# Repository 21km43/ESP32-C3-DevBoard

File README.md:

# ESP32-C3-DevBoard
ESP32-C3 Development Board. Made with [KiCAD 9.0](https://KiCAD.org)

You can get ESP32-C3-WROOM-02 from here.  
* [秋月電子](https://akizukidenshi.com/catalog/g/gM-17493/)  
* [DigiKey](https://www.digikey.jp/ja/products/detail/espressif-systems/ESP32-C3-WROOM-02-N4/14553031)
* [Mouser](https://www.mouser.jp/ProductDetail/Espressif-Systems/ESP32-C3-WROOM-02-N4?qs=stqOd1AaK7%2FqjTZKEOgfUg%3D%3D)

Orders can be placed by uploading data(Gerber, BOM, and CPL) to the JLCPCB. 
This project uses [Espressif Library for KiCAD](https://github.com/espressif/kicad-libraries). (It is available on Plugin & Contents manager.)  
Gerber, bom and cpl is placed on [production folder](/production) directory and Release. 

## Features
* Upload method: USB (Do not use GPIO 18 and 19 when downloading)
* USB: Type-C (USB 2.0)
* Regulator: [RT9080-33GJ5](https://www.richtek.com/Products/Linear%20Regulator/Single%20Output%20Linear%20Regulator/RT9080?sc_lang=en).
* External input voltage range: 4.3-6.5V (4.5V-5.5V is recommended)
* Power consumption (in deep sleep): 11.5µA (ESP32-C3: 5µA, RT9080-33GJ5: 6.5µA)

### Solder Jumpers
* JP1 ... VBUS = 5V jumper (Default: not connected): Connecting this disables the protective SBD between USB and external power supply. To eliminate the voltage drop due to SBD and output the voltage input from USB as it is to 5V, connect this jumper. Note that shorting this pin will increase current consumption by about 0.1mA due to the pull-down resistor on the CC pin.
* JP2 ... 5V -> 3.3V jumper (Default: connected): Connection of the external power supply terminal (5V pin) to the power input terminal to the ESP32-C3. Disconnect when suppressing regulator quiescent current.

## BOM
[BOM](/production/bom.csv)

### Notice

When using Fabrication-Toolkit, Please check "Apply automatic translations" option.

## 3D image

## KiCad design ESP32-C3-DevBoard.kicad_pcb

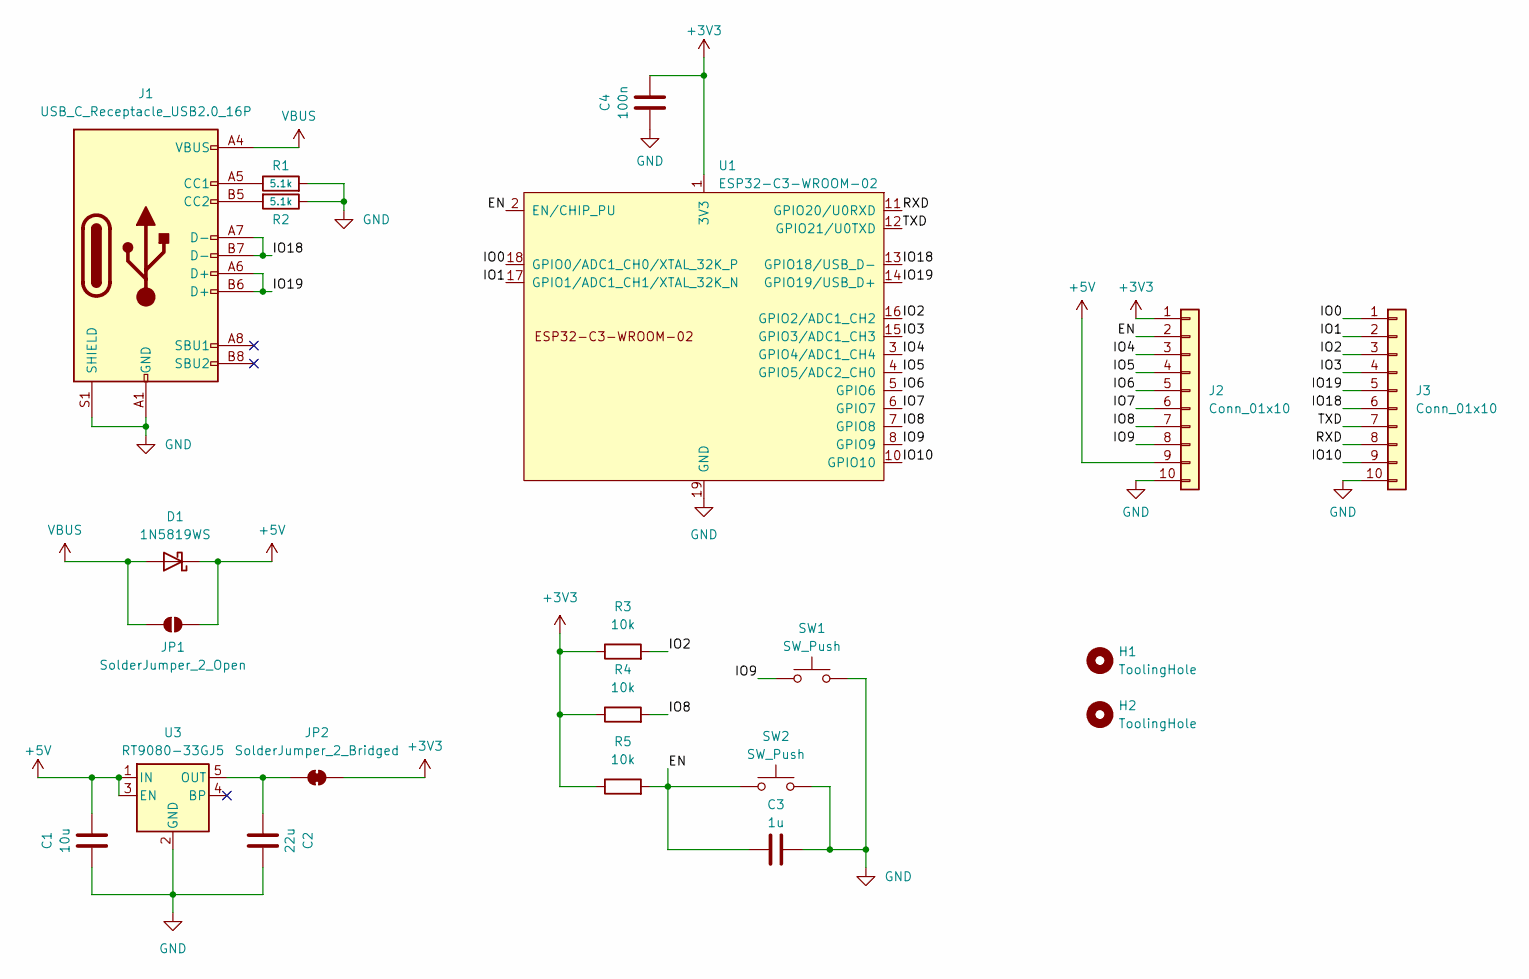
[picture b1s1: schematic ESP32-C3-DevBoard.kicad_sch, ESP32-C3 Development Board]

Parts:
C1: 10u; C_0805_2012Metric; LCSC Part # C15850
C2: 22u; C_0603_1608Metric; LCSC Part # C59461
C3: 1u; C_0402_1005Metric; LCSC Part # C52923
C4: 100n; C_0402_1005Metric; LCSC Part # C1525
D1: 1N5819WS; D_SOD-323; LCSC Part # C191023
H1, H2: ToolingHole; Tooling_Hole
J1: USB_C_Receptacle_USB2.0_16P; USB_C_Receptacle_XKB_U262-16XN-4BVC11; LCSC Part # C2988369
J2, J3: Conn_01x10; PinHeader_1x10_P2.54mm_Vertical
JP1: SolderJumper_2_Open; SolderJumper-2_P1.3mm_Open_RoundedPad1.0x1.5mm
JP2: SolderJumper_2_Bridged; SolderJumper-2_P1.3mm_Bridged_RoundedPad1.0x1.5mm
R1, R2: 5.1k; R_0402_1005Metric; LCSC Part # C25905
R3, R4, R5: 10k; R_0402_1005Metric; LCSC Part # C25744
SW1, SW2: SW_Push; SW_SPST_PTS810; LCSC Part # C115360
U1: ESP32-C3-WROOM-02; LCSC Part # C2934560
U3: RT9080-33GJ5; SOT-23-5; LCSC Part # C841192

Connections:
+3V3: C4.2, J2.1, JP2.2 (B), R3.1, R4.1, R5.1, U1.1 (3V3)
+5V: C1.2, D1.1 (K), J2.9, JP1.2 (B), U3.1 (IN), U3.3 (EN)
/EN: C3.1, J2.2, R5.2, SW2.1, U1.2 (EN/CHIP_PU)
/IO0: J3.1, U1.18 (GPIO0/ADC1_CH0/XTAL_32K_P)
/IO1: J3.2, U1.17 (GPIO1/ADC1_CH1/XTAL_32K_N)
/IO2: J3.3, R3.2, U1.16 (GPIO2/ADC1_CH2)
/IO3: J3.4, U1.15 (GPIO3/ADC1_CH3)
/IO4: J2.3, U1.3 (GPIO4/ADC1_CH4)
/IO5: J2.4, U1.4 (GPIO5/ADC2_CH0)
/IO6: J2.5, U1.5 (GPIO6)
/IO7: J2.6, U1.6 (GPIO7)
/IO8: J2.7, R4.2, U1.7 (GPIO8)
/IO9: J2.8, SW1.1, U1.8 (GPIO9)
/IO10: J3.9, U1.10 (GPIO10)
/IO18: J1.A7 (D-), J1.B7 (D-), J3.6, U1.13 (GPIO18/USB_D-)
/IO19: J1.A6 (D+), J1.B6 (D+), J3.5, U1.14 (GPIO19/USB_D+)
/RXD: J3.8, U1.11 (GPIO20/U0RXD)
/TXD: J3.7, U1.12 (GPIO21/U0TXD)
GND: C1.1, C2.2, C3.2, C4.1, J1.A1 (GND), J1.A12 (GND), J1.B1 (GND), J1.B12 (GND), J1.S1 (SHIELD), J2.10, J3.10, R1.2, R2.1, SW1.2, SW2.2, U1.9 (GND), U1.19 (GND), U3.2 (GND)
unnamed: J1.A5 (CC1), R1.1
unnamed: J1.B5 (CC2), R2.2
unnamed: C2.1, JP2.1 (A), U3.5 (OUT)
VBUS: D1.2 (A), J1.A4 (VBUS), J1.A9 (VBUS), J1.B4 (VBUS), J1.B9 (VBUS), JP1.1 (A)

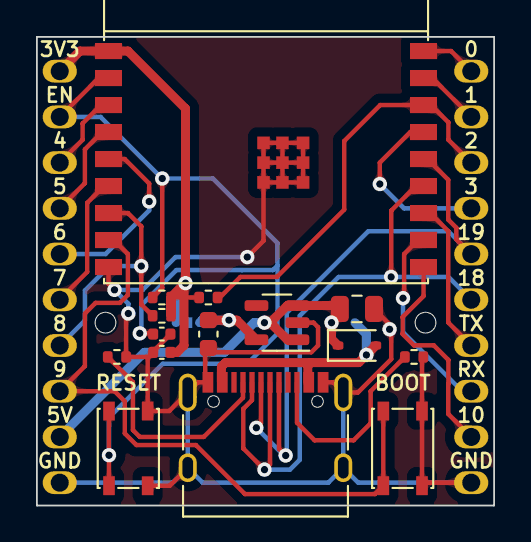
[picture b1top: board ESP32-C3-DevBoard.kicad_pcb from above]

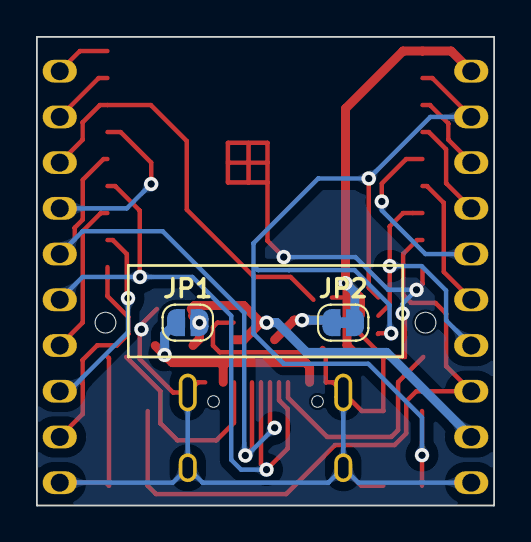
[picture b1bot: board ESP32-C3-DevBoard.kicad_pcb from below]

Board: 2 copper layers, 25.4 x 26.0 mm, 21 parts (4 on the bottom side), 23 nets.

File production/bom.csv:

Designator,Footprint,Quantity,Value,LCSC Part #
C1,0805,1,10u,C15850
C2,0603,1,22u,C59461
C3,0402,1,1u,C52923
C4,0402,1,100n,C1525
D1,D_SOD-323,1,1N5819WS,C191023
J1,USB_C_Receptacle_XKB_U262-16XN-4BVC11,1,USB_C_Receptacle_USB2.0_16P,C2988369
"R1, R2",0402,2,5.1k,C25905
"R3, R4, R5",0402,3,10k,C25744
"SW1, SW2",SW_SPST_PTS810,2,SW_Push,C115360
U1,ESP32-C3-WROOM-02,1,ESP32-C3-WROOM-02,C2934560
U3,SOT-23-5,1,RT9080-33GJ5,C841192

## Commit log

2023-10-11 add 3d model
2023-10-13 fix tooling hole position
2023-10-13 little fix
2023-10-15 fix silkscreen and tooling hole position
2023-11-19 Add Tooling Hole Library
2024-03-19 KiCAD 8.0
2024-04-10 gitignore
2024-05-24 change clearance
2024-05-27 solder jumper fix
2024-06-03 gitignoreと画像を更新
2024-06-07 show reference number
2024-06-07 jlcpcb offset fix
2024-06-07 mask fix
2024-06-07 reupload
2024-06-07 none
2024-06-07 pdf update
2024-06-08 change usb component
2024-06-09 avoid via on pad
2025-09-24 v1.1.1
2025-09-24 Update README with project details and features
2025-09-25 add fabrication-toolkit-options.json
2025-12-13 fix RT9080-33GJ5 description
2025-12-13 fix schematic
2026-04-29 fix: correct LCSC property name, font size for R1/R2, bump revision to v1.1.2
    Agent-Logs-Url: https://github.com/21km43/ESP32-C3-DevBoard/sessions/b7c18bea-2a61-483a-8d22-56899a96703c
2026-04-29 fix property name
2026-05-13 Add CI workflow for Fabrication Toolkit
